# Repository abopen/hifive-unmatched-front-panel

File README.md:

# HiFive Unmatched Front Panel

A custom front panel for the [SiFive HiFive Unmatched](https://www.sifive.com/boards/hifive-unmatched),
designed in KiCAD and featuring:

* OLED display
* Power button
* Reset button
* 2x GPIO buttons

With Python examples to drive the OLED display.

## Details

The display interfaces via I2C and operates on 3v3 logic levels, with the HiFive
Unmatched using 1v8 on its GPIO header, hence the board includes level shifting.

Power and reset buttons are connected to the Front Panel header.

An additional two buttons are provided for general use — e.g. screen pagination
— and these are connected to the GPIO header.

All the buttons are illuminated, however, this is not under software control and
the buttons simply illuminate when the HiFive Unmatched is powered on.

## Licence

HiFive Unmatched Front Panel is copyright 2021 Future Corporation.

The PCB design is published under the CERN Open Hardware Licence Version 2 -
Weakly Reciprocal (CERN-OHL-W).

The Python examples are published under the MIT License.

## About Future Corporation

[Future Corporation](https://www.future.co.jp/en/) in Japan is a company that conducts "IT Consulting & Service
Business" and "Innovation Business" through the use of latest technology. 
Since the founding in 1989, we have designed and improved the business of our
clients through developing systems that integrates business management with IT.
Our clients are from various industries including Finance, Manufacturing,
Distribution and Logistics. 
We have also created our own new services based on the know-how we have
accumulated in this process.
We are contributing to the society by promoting innovation and creating new
values for clients that is based on the strengths of "connoisseurship" and
"implementation ability" of latest technologies such as AI and robotics.

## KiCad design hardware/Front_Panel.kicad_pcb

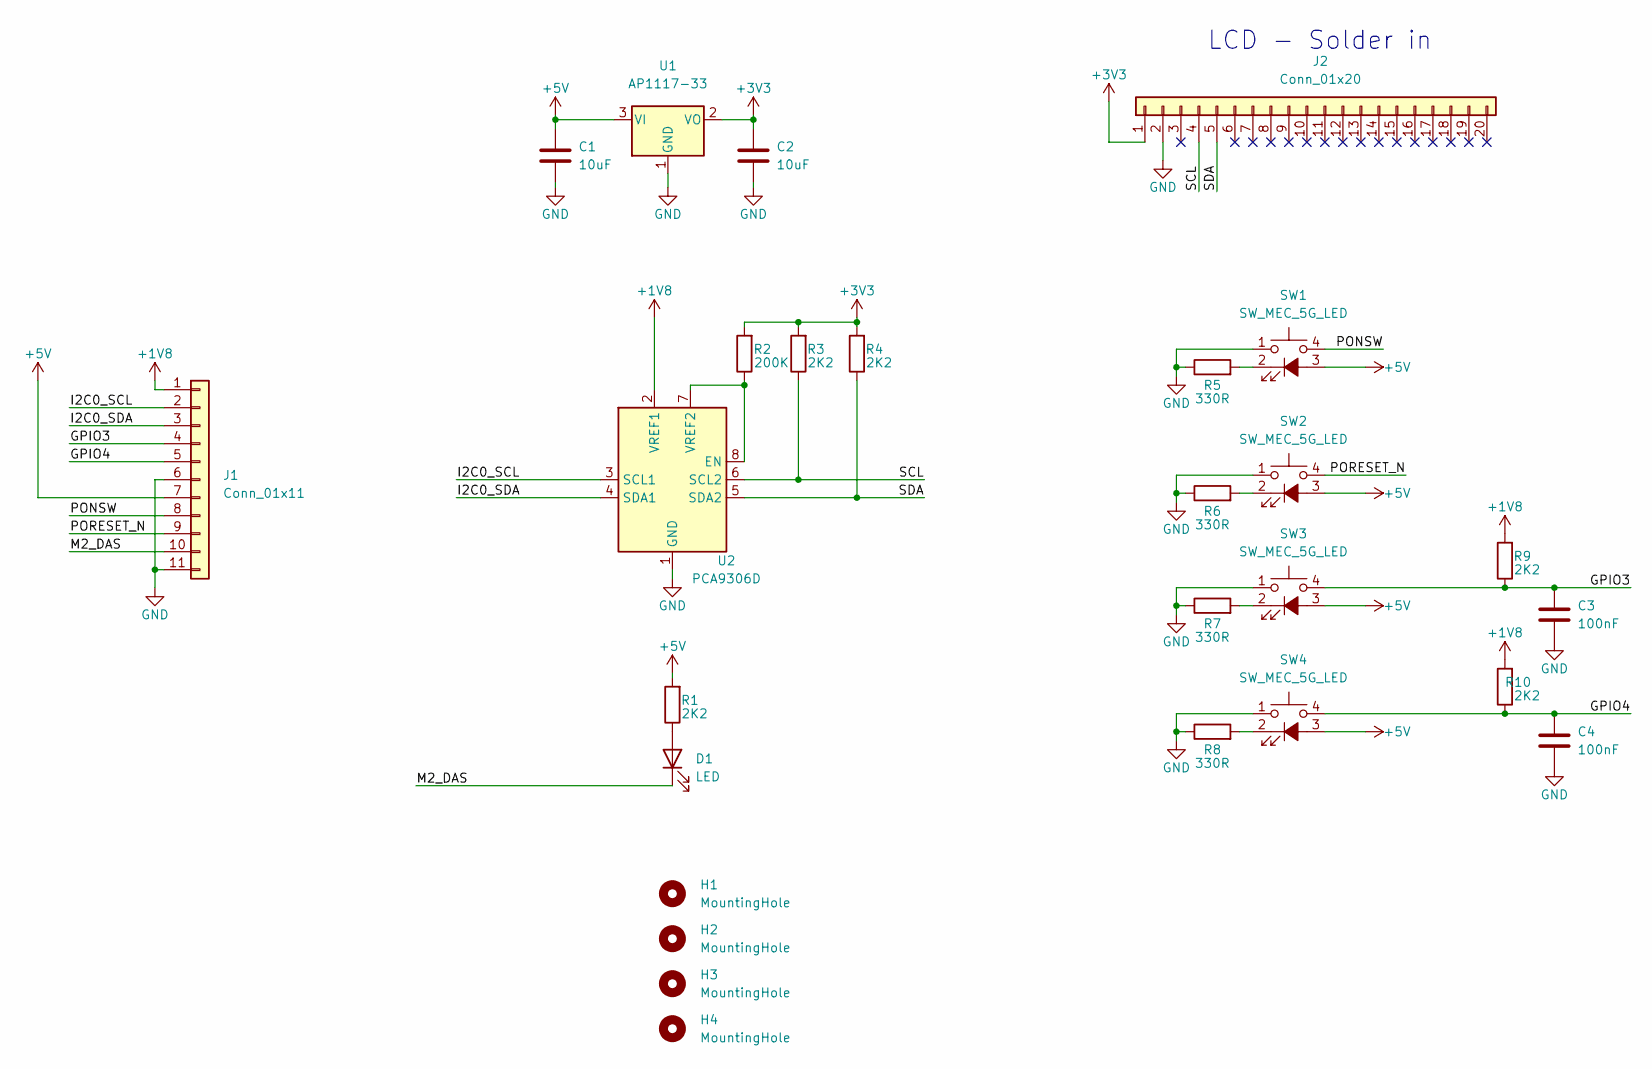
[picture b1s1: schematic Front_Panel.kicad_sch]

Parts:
C1, C2: 10uF; C_0603_1608Metric
C3, C4: 100nF; C_0603_1608Metric
D1: LED; LED_0805_2012Metric
H1, H2, H3, H4: MountingHole; MountingHole_3.2mm_M3
J1: Conn_01x11; Molex_KK-254_AE-6410-11A_1x11_P2.54mm_Vertical
J2: Conn_01x20; PinHeader_1x20_P2.54mm_Vertical
R1, R3, R4, R9, R10: 2K2; R_0603_1608Metric
R2: 200K; R_0603_1608Metric
R5, R6, R7, R8: 330R; R_0603_1608Metric
SW1, SW2, SW3, SW4: SW_MEC_5G_LED
U1: AP1117-33; SOT-223-3_TabPin2
U2: PCA9306D; SO-8_3.9x4.9mm_P1.27mm

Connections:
+1V8: J1.1, R9.2, R10.2, U2.2 (VREF1)
+3V3: C2.1, J2.1, R2.2, R3.2, R4.2, U1.2 (VO)
+5V: C1.1, J1.7, R1.2, SW1.3 (K), SW2.3 (K), SW3.3 (K), SW4.3 (K), U1.3 (VI)
/GPIO3: C3.1, J1.4, R9.1, SW3.4 (A)
/GPIO4: C4.1, J1.5, R10.1, SW4.4 (A)
/I2C0_SCL: J1.2, U2.3 (SCL1)
/I2C0_SDA: J1.3, U2.4 (SDA1)
/M2_DAS: D1.1 (K), J1.10
/PONSW: J1.8, SW1.4 (A)
/PORESET_N: J1.9, SW2.4 (A)
/SCL: J2.4, R3.1, U2.6 (SCL2)
/SDA: J2.5, R4.1, U2.5 (SDA2)
GND: C1.2, C2.2, C3.2, C4.2, J1.6, J1.11, J2.2, R5.1, R6.1, R7.1, R8.1, SW1.1, SW2.1, SW3.1, SW4.1, U1.1 (GND), U2.1 (GND)
unnamed: D1.2 (A), R1.1
unnamed: R2.1, U2.7 (VREF2), U2.8 (EN)
unnamed: R5.2, SW1.2
unnamed: R6.2, SW2.2
unnamed: R7.2, SW3.2
unnamed: R8.2, SW4.2
no_connect_20: J2.10
no_connect_21: J2.11
no_connect_22: J2.12
no_connect_23: J2.13
no_connect_24: J2.14
no_connect_25: J2.15
no_connect_26: J2.16
no_connect_27: J2.17
no_connect_28: J2.18
no_connect_29: J2.19
no_connect_30: J2.20
no_connect_31: J2.3
no_connect_32: J2.6
no_connect_33: J2.7
no_connect_34: J2.8
no_connect_35: J2.9

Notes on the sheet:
LCD - Solder in

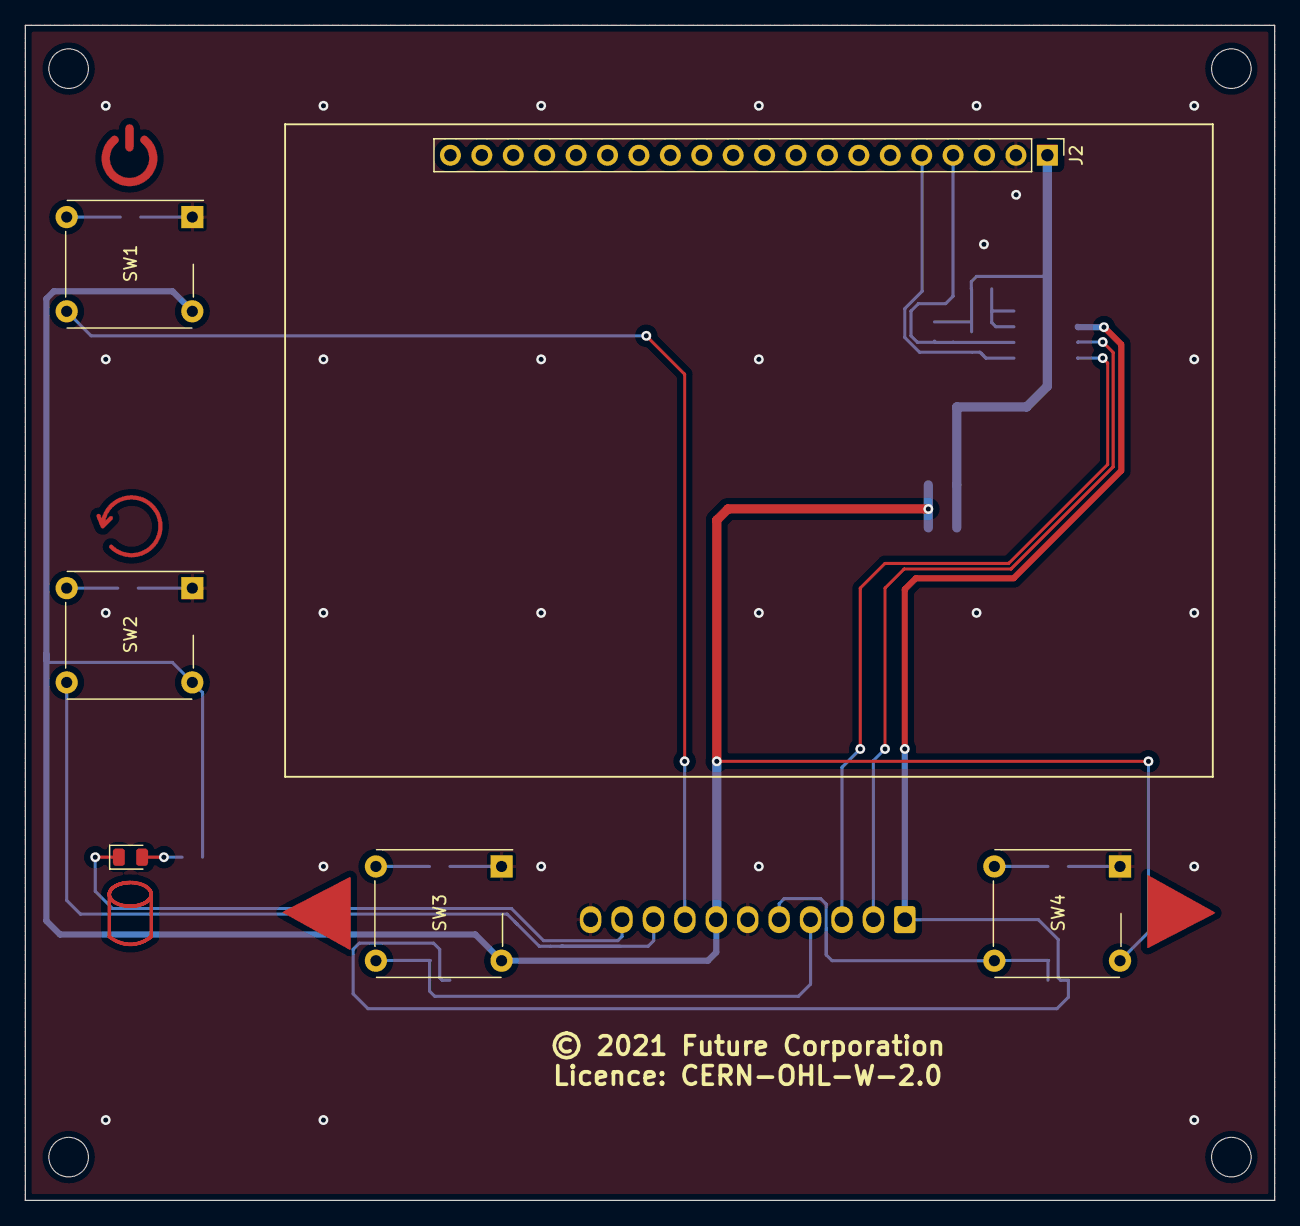
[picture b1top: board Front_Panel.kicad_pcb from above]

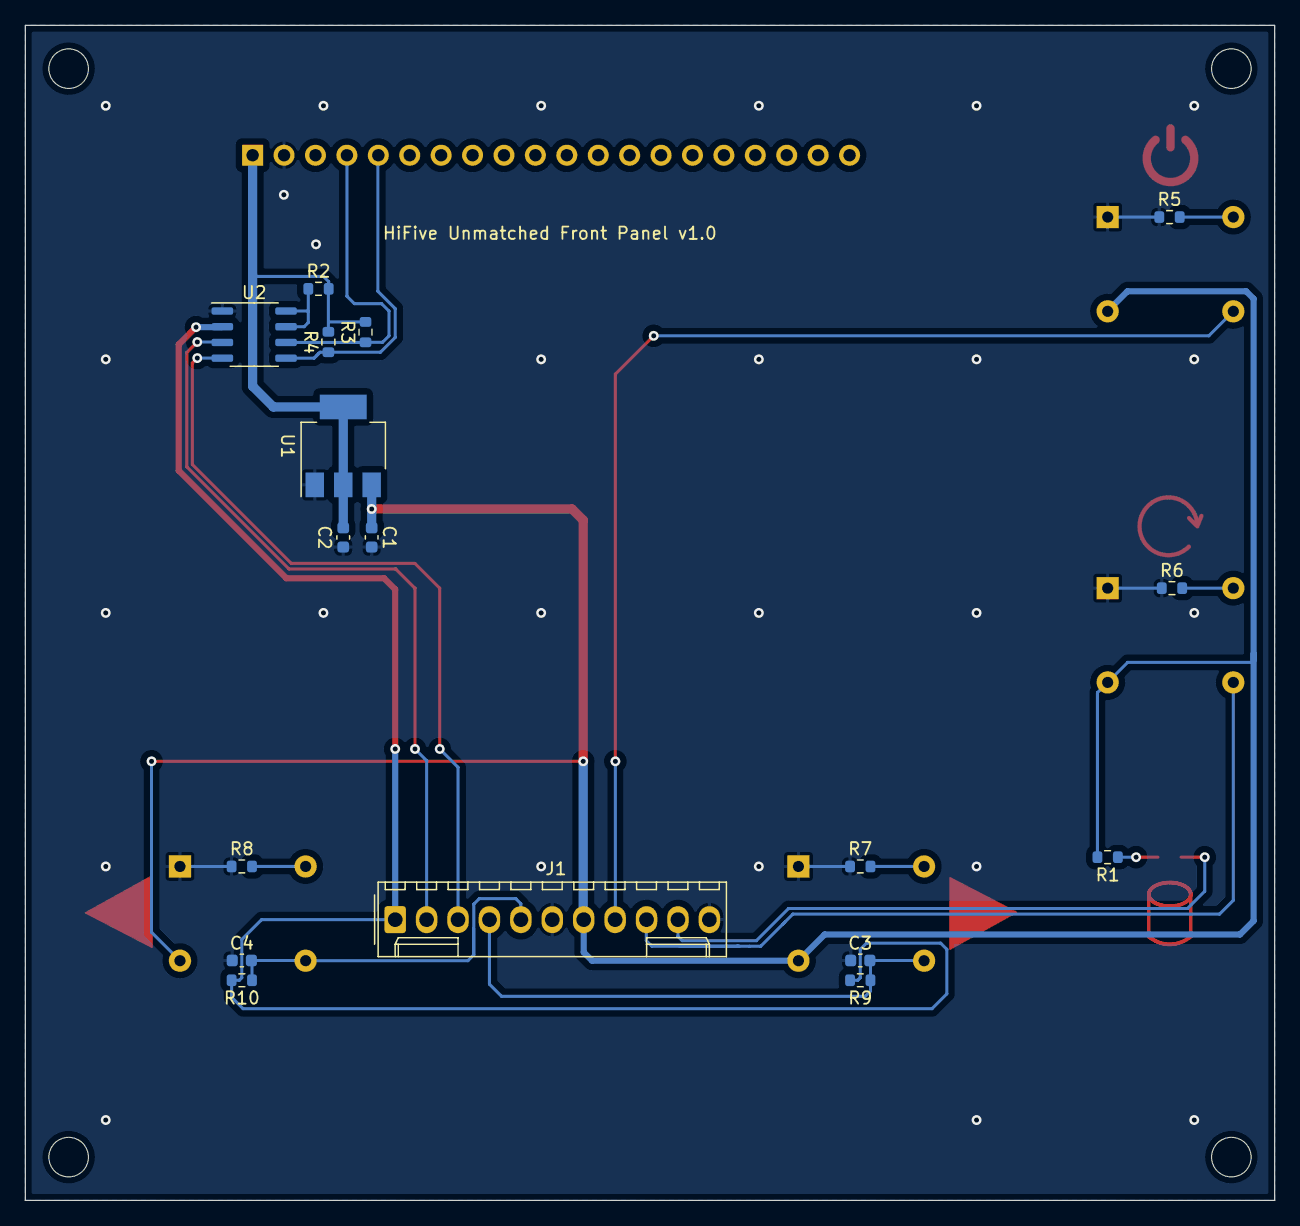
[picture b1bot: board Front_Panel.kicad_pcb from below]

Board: 2 copper layers, 101.0 x 95.0 mm, 27 parts (17 on the bottom side), 19 nets.

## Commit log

2021-11-03 Add hardware
2021-11-09 Add board image
2021-11-09 Added software and licensing.

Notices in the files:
hardware/Front_Panel.kicad_pcb:
© 2021 Future Corporation
Licence: CERN-OHL-W-2.0
